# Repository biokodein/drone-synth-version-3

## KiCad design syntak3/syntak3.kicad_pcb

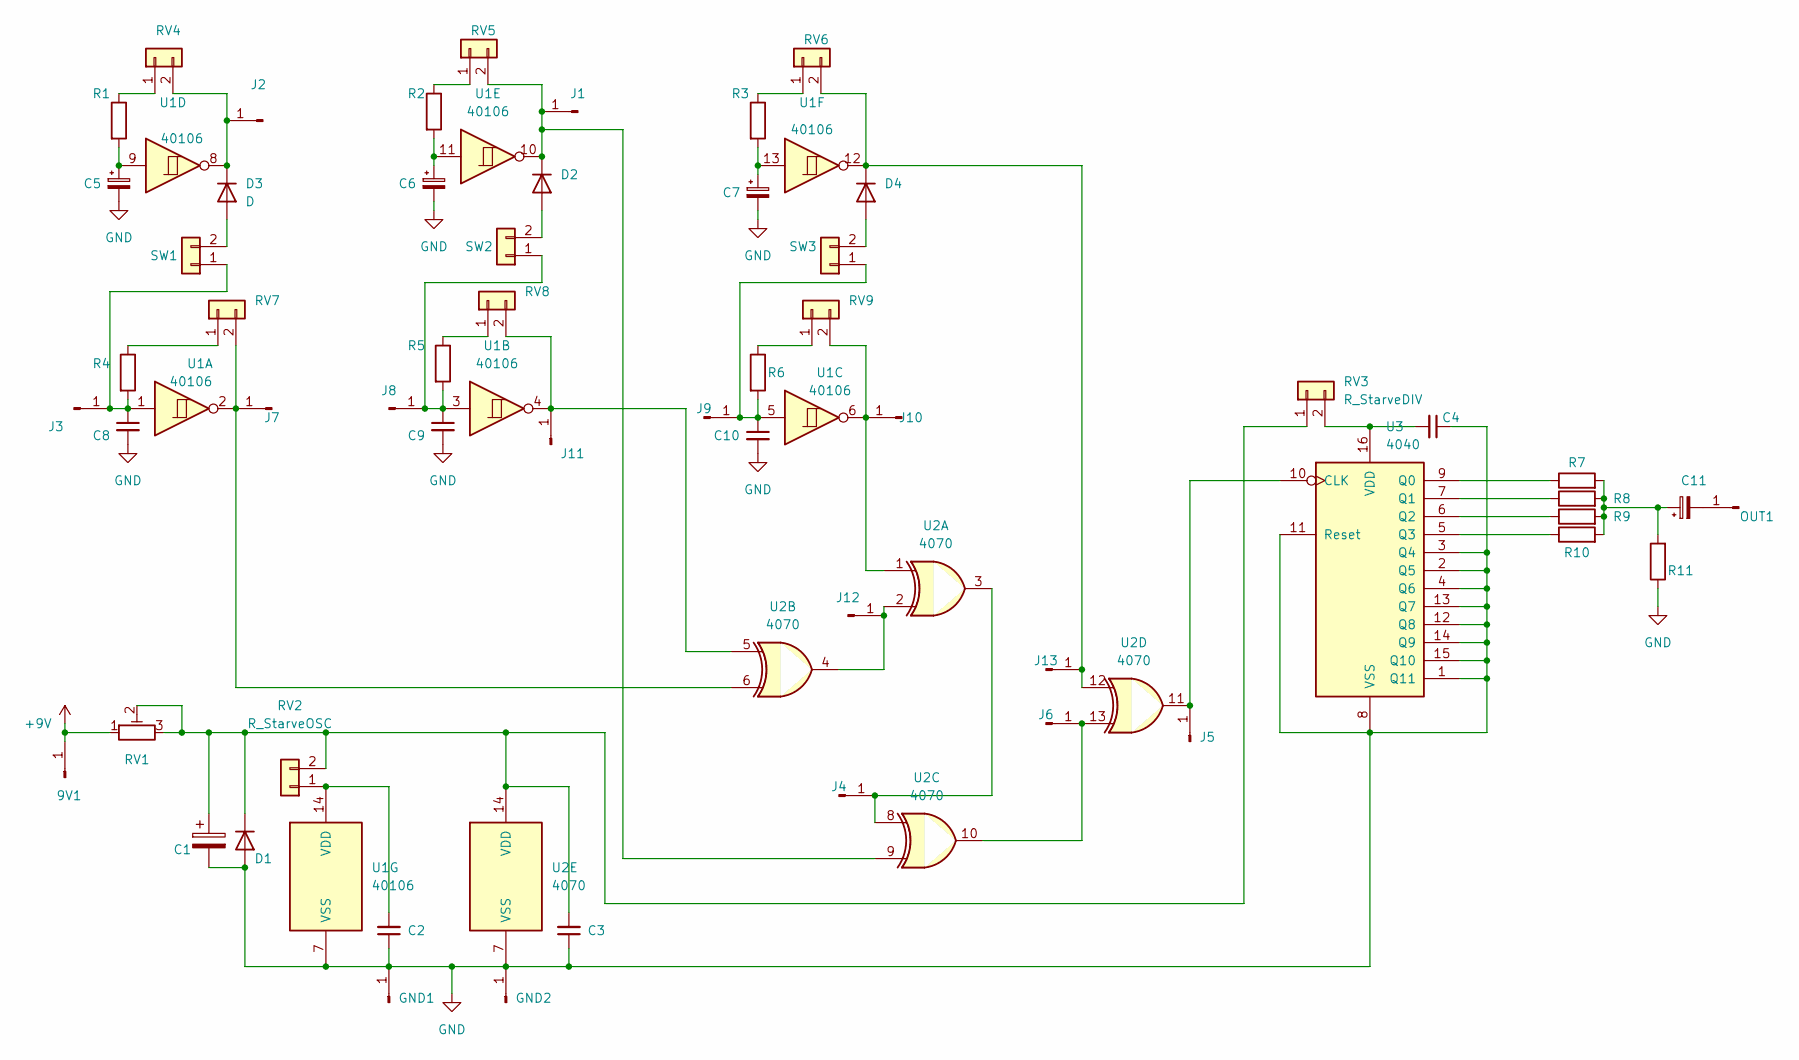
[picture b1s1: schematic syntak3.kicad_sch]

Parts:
9V1: Conn_01x01_Pin; SolderWire-0.5sqmm_1x01_D0.9mm_OD2.1mm
C1: C_Polarized; CP_Radial_D13.0mm_P5.00mm
C2, C3, C4, C8, C9, C10: C_Small; C_MLCC_D4.3mm_W1.9mm_P5.00mm
C5, C6, C7, C11: C_Polarized_Small; CP_Electro_Radial_D5.0mm_P2.50mm
D1, D2, D3, D4: D; DIODE_DO-35_SOD27_P7.62mm_Horizontal
GND1, GND2: Conn_01x01_Pin; SolderWire-0.5sqmm_1x01_D0.9mm_OD2.1mm
J1, J2, J3, J4, J5, J6, J7, J8, J9, J10, J11, J12, J13: Conn_01x01_Pin; SolderWire-0.5sqmm_1x01_D0.9mm_OD2.1mm
OUT1: Conn_01x01_Pin; SolderWire-0.5sqmm_1x01_D0.9mm_OD2.1mm
R1, R2, R3, R4, R5, R6, R7, R8, R9, R10, R11: R; RES_0.25watt_L3.6mm_D1.6mm_P7.62mm_Horizontal
RV1: R_Potentiometer_Trim; Potentiometer_Runtron_RM-065_Vertical
RV2: R_StarveOSC; RV-cermet; Part Number 1-0201FBV0T
RV3: R_StarveDIV; RV-cermet; Part Number 1-0201FBV0T
RV4, RV5, RV6, RV7, RV8, RV9: R_Potentiometer; RV-cermet; Part Number 1-0201FBV0T
SW1, SW2, SW3: Socket_01x02; CONN_1x02_P2.54mm_Vertical; Part Number ?
U1: 40106; DIP-14_W7.62mm_Socket_LongPads
U2: 4070; DIP-14_W7.62mm_Socket_LongPads
U3: 4040; DIP-16_W7.62mm_Socket_LongPads

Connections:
+9V: 9V1.1, RV1.1; also elsewhere on the board
GND: C1.2, C2.1, C3.1, C4.1, C5.2, C6.2, C7.2, C8.2, C9.2, C10.2, D1.2 (A), GND1.1, GND2.1, R11.1, U1.7 (VSS), U2.7 (VSS), U3.1 (Q11), U3.2 (Q5), U3.3 (Q4), U3.4 (Q6), U3.8 (VSS), U3.11 (Reset), U3.12 (Q8), U3.13 (Q7), U3.14 (Q9), U3.15 (Q10); also elsewhere on the board
unnamed 2: C5.1, R1.2, U1.9; also elsewhere on the board
unnamed 3: C6.1, R2.2, U1.11; also elsewhere on the board
unnamed 4: C7.1, R3.2, U1.13; also elsewhere on the board
unnamed: C11.1, R7.2, R8.2, R9.2, R10.2, R11.2
unnamed 6: C1.1, C3.2, D1.1 (K), RV1.2, RV1.3, RV2.2, RV3.1, U2.14 (VDD); also elsewhere on the board
unnamed: D2.2 (A), SW2.2
unnamed 8: D2.1 (K), J1.1, RV5.2, U1.10, U2.9; also elsewhere on the board
unnamed: D3.2 (A), SW1.2
unnamed 10: D3.1 (K), J2.1, RV4.2, U1.8; also elsewhere on the board
unnamed: D4.2 (A), SW3.2
unnamed 12: D4.1 (K), J13.1, RV6.2, U1.12, U2.12; also elsewhere on the board
unnamed 13: C8.1, J3.1, R4.2, SW1.1, U1.1; also elsewhere on the board
unnamed 14: J4.1, U2.3, U2.8; also elsewhere on the board
unnamed 15: J5.1, U2.11, U3.10 (CLK); also elsewhere on the board
unnamed 16: J6.1, U2.10, U2.13; also elsewhere on the board
unnamed 17: J7.1, RV7.2, U1.2, U2.6; also elsewhere on the board
unnamed 18: C9.1, J8.1, R5.2, SW2.1, U1.3; also elsewhere on the board
unnamed 19: C10.1, J9.1, R6.2, SW3.1, U1.5; also elsewhere on the board
unnamed 20: J10.1, RV9.2, U1.6, U2.1; also elsewhere on the board
unnamed 21: J11.1, RV8.2, U1.4, U2.5; also elsewhere on the board
unnamed 22: J12.1, U2.2, U2.4; also elsewhere on the board
unnamed: C11.2, OUT1.1
unnamed 24: C2.2, RV2.1, U1.14 (VDD); also elsewhere on the board
unnamed 25: C4.2, RV3.2, U3.16 (VDD); also elsewhere on the board
unnamed: R1.1, RV4.1
unnamed: R2.1, RV5.1
unnamed: R3.1, RV6.1
unnamed: R4.1, RV7.1
unnamed: R5.1, RV8.1
unnamed: R6.1, RV9.1
unnamed 32: R7.1, U3.9 (Q0); also elsewhere on the board
unnamed 33: R8.1, U3.7 (Q1); also elsewhere on the board
unnamed 34: R9.1, U3.6 (Q2); also elsewhere on the board
unnamed 35: R10.1, U3.5 (Q3); also elsewhere on the board

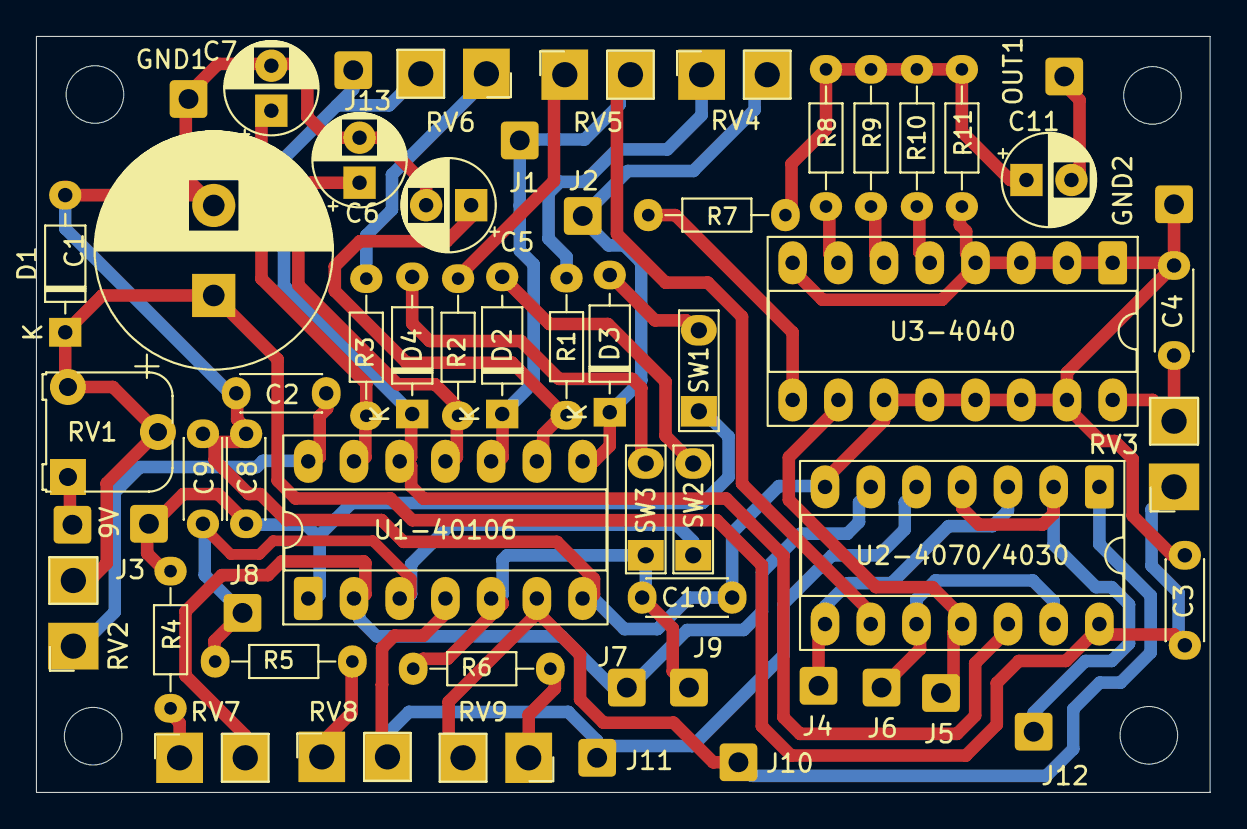
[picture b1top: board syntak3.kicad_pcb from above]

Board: 2 copper layers, 65.2 x 42.0 mm, 58 parts (0 on the bottom side), 36 nets.

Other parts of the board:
9V: Conn_01x01_Pin; SolderWire-0.5sqmm_1x01_D0.9mm_OD2.1mm
U1-40106: 40106; DIP-14_W7.62mm_Socket_LongPads
U2-4070/4030: 4070; DIP-14_W7.62mm_Socket_LongPads
U3-4040: 4040; DIP-16_W7.62mm_Socket_LongPads

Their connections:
+9V: 9V.1; also elsewhere on the board
GND: U1-40106.7 (VSS), U2-4070/4030.7 (VSS), U3-4040.1 (Q11), U3-4040.2 (Q5), U3-4040.3 (Q4), U3-4040.4 (Q6), U3-4040.8 (VSS), U3-4040.11 (Reset), U3-4040.12 (Q8), U3-4040.13 (Q7), U3-4040.14 (Q9), U3-4040.15 (Q10); also elsewhere on the board
unnamed 2: U1-40106.9; also elsewhere on the board
unnamed 3: U1-40106.11; also elsewhere on the board
unnamed 4: U1-40106.13; also elsewhere on the board
unnamed 6: U2-4070/4030.14 (VDD); also elsewhere on the board
unnamed 8: U1-40106.10, U2-4070/4030.9; also elsewhere on the board
unnamed 10: U1-40106.8; also elsewhere on the board
unnamed 12: U1-40106.12, U2-4070/4030.12; also elsewhere on the board
unnamed 13: U1-40106.1; also elsewhere on the board
unnamed 14: U2-4070/4030.3, U2-4070/4030.8; also elsewhere on the board
unnamed 15: U2-4070/4030.11, U3-4040.10 (CLK); also elsewhere on the board
unnamed 16: U2-4070/4030.10, U2-4070/4030.13; also elsewhere on the board
unnamed 17: U1-40106.2, U2-4070/4030.6; also elsewhere on the board
unnamed 18: U1-40106.3; also elsewhere on the board
unnamed 19: U1-40106.5; also elsewhere on the board
unnamed 20: U1-40106.6, U2-4070/4030.1; also elsewhere on the board
unnamed 21: U1-40106.4, U2-4070/4030.5; also elsewhere on the board
unnamed 22: U2-4070/4030.2, U2-4070/4030.4; also elsewhere on the board
unnamed 24: U1-40106.14 (VDD); also elsewhere on the board
unnamed 25: U3-4040.16 (VDD); also elsewhere on the board
unnamed 32: U3-4040.9 (Q0); also elsewhere on the board
unnamed 33: U3-4040.7 (Q1); also elsewhere on the board
unnamed 34: U3-4040.6 (Q2); also elsewhere on the board
unnamed 35: U3-4040.5 (Q3); also elsewhere on the board

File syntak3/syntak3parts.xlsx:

| Reference | Qty | Value in kit | Value range | Note | Footprint
connect with wires | volume control potentiometer | 1 | 100K linear or log
 | stereo jack audio output | 1 | 6.3 mm stereo jack | optionally 3.5 mm | can use mono jack plus on/off switch
 | wire | 3-4 m | 26 awg stranded | 24-26 awg
 | extra buttons | 0+ | momentary button (normally OFF) |  | connect to solder points labeled J1-J13, try
 | SW1,SW2,SW3 | 3 | momentary button (normally ON) |  |  | CONN_1x02_P5mm
 | RV4,RV5,RV6,RV7,RV8,RV9 | 6 | 1M linear/photoresistor |  |  | CONN_1x02_P2.54mm
 | RV3 | 1 |  |  |  | CONN_1x02_P2.54mm
 | RV2 | 1 | 10K linear |  |  | CONN_1x02_P2.54mm
 | 9V battery | 1
 | 9V battery holder | 1
 | 9V battery clip | 1
on board | DIP socket 14 pin | 2 |  |  |  | Package_DIP:DIP-14_W7.62mm_Socket_LongPads
 | DIP socket 16 pin | 1 |  |  |  | Package_DIP:DIP-16_W7.62mm_Socket_LongPads
 | U1 | 1 | CD40106 |  |  | Package_DIP:DIP-14_W7.62mm
 | U2 | 1 | CD4070 or CD4030 |  |  | Package_DIP:DIP-14_W7.62mm
 | U3 | 1 | CD4040 |  |  | Package_DIP:DIP-16_W7.62mm
 | RV1 | 1 | 500R trimmer | under 1K |  | Potentiometer_THT:Potentiometer_Runtron_RM-065_Vertical
 | R1,R2,R3,R4,R5,R6 | 6 | 10K | 1K-47K |  | RES_0.25watt_L3.6mm_D1.6mm_P7.62mm_Horizontal
 | R7,R8,R9,R10 | 4 | 10K | 4.7K-22K |  | RES_0.25watt_L3.6mm_D1.6mm_P7.62mm_Horizontal
 | R11 | 1 | 47K |  |  | RES_0.25watt_L3.6mm_D1.6mm_P7.62mm_Horizontal
 | D1 | 1 | 4007 | 4001 or similar |  | DIODE_DO-35_SOD27_P7.62mm_Horizontal
 | D2,D3,D4 | 3 | 4148 | optionally LEDs |  | DIODE_DO-35_SOD27_P7.62mm_Horizontal
 | C1 | 1 | 3300 uF electrolytic | 1000-4700 uF |  | Capacitor_THT:CP_Radial_D13.0mm_P5.00mm
 | C2,C3,C4 | 3 | 10 nF ceramic | 10-100 nF |  | C_MLCC_D4.3mm_W1.9mm_P5.00mm
 | C5,C6,C7 | 3 | 1 or 2.2 uF electrolytic | 10 nF - 22 uF | get DPDT lever switches to make oscillator range selectable | CP_Electro_Radial_D5.0mm_P2.50mm
 | C8,C9,C10 | 3 | 10 nF ceramic | 4.7-47 nF |  | C_MLCC_D4.3mm_W1.9mm_P5.00mm
 | C11 | 1 | 22 uF electrolytic | 10-47 uF |  | CP_Electro_Radial_D5.0mm_P2.50mm
